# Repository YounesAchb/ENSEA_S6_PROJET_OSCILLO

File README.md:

# ENSEA S6 — Projet Oscilloscope Portable Connecté

Ce dépôt contient l'intégralité des sources (conception matérielle KiCad, firmware STM32 et application Java Android) du projet de fin de S6 réalisé à l'ENSEA. 

## 👥 Étudiants concernés
* **Yassine JABOU**
* **Younes ACHBAD**
* **Gabriel BOUDOUX D'HAUTEFEUILLE**
* **Gökay OZDEN**

---

## 📝 Abstract & Contexte de Fin de Projet
Le but de ce projet est de concevoir un système embarqué autonome agissant comme un oscilloscope de précision déporté. L'écosystème est divisé en deux parties principales :
1. **Un boîtier d'acquisition autonome :** Reçoit le signal analogique, adapte son amplitude, le numérise via un STM32L476RG et transmet les trames via un module Bluetooth HC-05.
2. **Une interface utilisateur (Display) :** Une application Android native développée en Java permettant la visualisation en temps réel, le contrôle des calibres, les mesures par curseurs et le traitement fréquentiel (FFT).

⚠️ **Statut Réel du Projet (Post-Soutenance) :** Suite à un retard de livraison critique de notre fournisseur sur le composant analogique central (l'amplificateur à gain programmable PGA849), le PCB final n'a pas pu être assemblé et soudé à temps pour les tests physiques. 
Cependant, l'ensemble du projet a été validé avec succès par une **approche de virtualisation et de simulation** :
* **Hardware :** PCB double couche entièrement routé et validé par DRC sous KiCad.
* **Firmware C :** 100% fonctionnel, validé sur carte Nucleo en simulant l'absence du PGA.
* **Application Android :** 100% fonctionnelle, dotée d'un banc de simulation générant des signaux virtuels cohérents permettant de valider l'interface utilisateur, le protocole de communication et les algorithmes de traitement (FFT, curseurs).

---

## 🛠 Spécifications du Projet

### 1. Performances & Objectifs Communs
* **Nombre d'entrées :** 2 voies (1 voie implémentée et validée sur cette version).
* **Bande passante visée :** 10 Hz - 50 kHz.
* **Résolution d'acquisition :** 12 bits.
* **Échantillonnage :** 10 kHz fixe, rythmé de manière matérielle par Timer.
* **Points par capture :** Buffer circulaire de 1024 points (gestion par demi-tableaux de 512 points).
* **Communication :** Liaison Bluetooth SPP (Standard Serial Port Profile) à 115200 bauds.
* **Gestion de l'énergie :** Objectif d'autonomie de 6 heures sur piles (sélection de composants Low-Power).

### 2. Architecture Matérielle (Hardware)

Le routage a été optimisé sur un PCB compact double couche. La conception repose sur une séparation stricte des masses et une cascade d'alimentation spécifique pour préserver la propreté du signal de référence ($V_{ref}$) de l'ADC.

#### Schéma Bloc de l'Architecture Électronique
```mermaid
graph TD
    classDef power fill:#2d3436,stroke:#deff9a,stroke-width:2px,color:#fff;
    classDef analog fill:#d63031,stroke:#fff,stroke-width:2px,color:#fff;
    classDef digital fill:#0984e3,stroke:#fff,stroke-width:2px,color:#fff;
    classDef com fill:#00b894,stroke:#fff,stroke-width:2px,color:#fff;

    subgraph Alimentation & Énergie
        Piles((Piles 3xAA)) -->|BAT_PLUS| Switch[Interrupteur + Diode Schottky]
        Switch -->|Vin| LDO3[LDO 3.3V: AP2112K]:::power
        Switch -->|Vin| LDO5[LDO 5V: MCP1826S]:::power
        LDO5 -->|Sortie 5V| Traco[DC/DC Symétrique: Traco TSM]:::power
        Traco -->|+15V / -15V| PGA
    end

    subgraph Chaîne Analogique
        BNC((BNC Verticale 50Ω)) -->|Signal Brut| PGA[Ampli de précision: PGA849]:::analog
        PGA -->|Signal Conditionné| Clamping[Diode de protection: BAT54S]:::analog
        Clamping -->|Entrée Analogique PA0| MCU
    end

    subgraph Traitement & Communication
        LDO3 -->|V3.3_DIG| MCU[MCU: STM32L476RG]:::digital
        MCU -->|Sélection Calibre 3-bits| PGA
        LDO5 -->|5V BT| BT[Module Bluetooth: HC-05]:::com
        MCU <-->|UART 115200 bauds| BT
        BT -.->|Sans-fil SPP| Android((App Android Java)):::com
    end

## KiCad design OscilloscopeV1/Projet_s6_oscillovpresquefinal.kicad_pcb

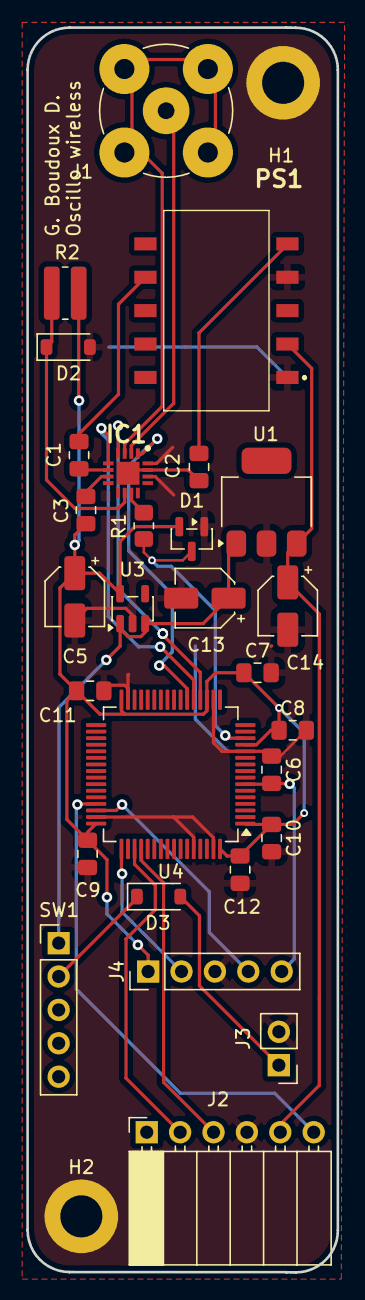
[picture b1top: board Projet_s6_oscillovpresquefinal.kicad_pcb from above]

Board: 2 copper layers, 23.6 x 94.7 mm, 30 parts (0 on the bottom side), 25 nets.

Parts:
C1, C2, C3, C6, C7, C8, C9, C10, C11, C12: 100 nF; C_0805_2012Metric_Pad1.18x1.45mm_HandSolder
C5, C13, C14: 10µ; CP_Elec_4x5.7
D1: BAT54S; SOT-23
D2: D_Zener; D_SOD-123
D3: D_Schottky; D_SOD-123
H1, H2: MountingHole_Pad; MountingHole_3.2mm_M3_DIN965_Pad
IC1: PGA849RGTR; QFN50P300X300X100-17N-D
J1: Conn_Coaxial; BNC_TEConnectivity_1478204_Vertical
J2: Conn_01x06_Socket; PinSocket_1x06_P2.54mm_Horizontal
J3: PILES_3AA; PinHeader_1x02_P2.54mm_Vertical
J4: Conn_01x05_Pin; PinHeader_1x05_P2.54mm_Vertical
PS1: TSM_0515D; TSM0515D
R1: 1k; R_0805_2012Metric_Pad1.20x1.40mm_HandSolder
R2: 1,35k; R_0815_2038Metric_Pad1.20x4.05mm_HandSolder
SW1: SW_SPST; PinHeader_1x05_P2.54mm_Vertical
U1: MCP1826S; SOT-223
U3: AP2112K-3.3; SOT-23-5
U4: STM32L476RGTx; LQFP-64_10x10mm_P0.5mm

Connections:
ANL0: IC1.4 (A0), U4.20 (PA4)
ANL1: IC1.5 (A1), U4.21 (PA5)
ANL2: IC1.1 (A2), U4.22 (PA6)
BAT_PLUS: C13.1, SW1.1 (A), U1.1 (VI), U3.1 (VIN), U3.3 (EN)
Entree_adc: D1.3 (COM), R1.1, U4.14 (PA0)
GND: C5.2, C6.1, C7.2, C8.2, C9.2, C10.2, C11.2, C12.2, C13.2, C14.2, D1.1 (A), D2.2 (A), H1.1, H2.1, IC1.14 (LVSS), IC1.16 (DGND), J2.4, J3.2, J4.3, PS1.1 (-VIN), PS1.7 (COM), U1.2 (GND), U3.2 (GND), U4.12 (VSSA), U4.18 (VSS), U4.31 (VSS), U4.47 (VSS), U4.60 (BOOT0), U4.63 (VSS)
KEY: J2.6, U4.45 (PA12)
NRST: C6.2, J4.5, U4.7 (NRST)
unnamed: D3.2 (A), J3.1
unnamed: D3.1 (K), SW1.2 (B)
unnamed: C2.2, IC1.15 (VS-), IC1.17 (EP)
unnamed: IC1.2 (IN+), J1.1 (In)
unnamed: IC1.3 (IN-), J1.2 (Ext)
unnamed: C3.1, IC1.7 (LVDD)
unnamed: C1.1, IC1.6 (VS+)
SGN_Sortie: IC1.11 (OUT), R1.2
SWCLK: J4.2, U4.49 (PA14)
SWDIO: J4.4, U4.46 (PA13)
Sortie5V: C14.1, J2.5, PS1.3 (+VIN), U1.3 (VO)
Traco_+15V: C1.2, PS1.12 (+VO)
Traco_-15V: C2.1, PS1.9 (-VO)
UART_RX: J2.3, U4.52 (PC11)
UART_TX: J2.2, U4.51 (PC10)
V3.3_DIG: C3.2, C5.1, C7.1, C8.1, C9.1, C10.1, C11.1, C12.1, D1.2 (K), J4.1, R2.1, U3.5 (VOUT), U4.1 (VBAT), U4.13 (VDDA), U4.19 (VDD), U4.32 (VDD), U4.48 (VDDUSB), U4.64 (VDD)
Vref_1.5: D2.1 (K), IC1.10 (REF), R2.2

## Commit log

2026-02-09 Create ALIMENTATION.md
    Descriptif du système d'alimentation
2026-02-09 Update ALIMENTATION.md
    Ajout d'explication pour les 2 résistances de 100kOhm
2026-02-09 Update SOURCING COMPOSANTS - Feuille 1.pdf
    Rajout et mise au propre du sourcing
2026-02-09 name correction
2026-02-16 Ajout de la Librairie des composants
2026-02-16 Addition du schematic partie analogique
2026-02-16 schematic adc v2
    pin for HC05, improvment of pont diviseur
2026-02-16 Partie Alim
    A completer
2026-02-16 Version Presque final du schematics
2026-02-18 Add files via upload
    c'est juste la partie écran
2026-02-18 Add files via upload
    Voici la partie bluetooth
2026-02-18 v4
    Addition of zener instead of op amp for generating 1.5V
2026-02-19 Partie Alim Fini
2026-03-08 Ajout du connecteur SWD et des fixations
2026-03-09 Résolution de toutes les erreurs ERC
2026-03-09 Restructuration de l'architecture du projet
    J'ai mis le schéma dans un projet , il est auparavant appart il se trouve désormais dans le dossier Oscillo_Y
2026-03-09 Ajout des Empreintes pour PGA et pour le Traco ( TSM )
2026-03-09 Plus d'erreur ERC et empreintes du traco et pga
2026-03-09 Restructuration des fichiers
2026-03-09 Ajout du schématique final
2026-03-09 Modification du système d'alimentation / tension de 1,5V
    Modification du système d'alimentation et remplacement du suiveur par une diode zener
2026-03-09 Ajout de toutes les empreintes
2026-03-09 Finalisation Empreinte
2026-03-09 Avancement PCB
2026-03-09 Add files via upload
    Version finale 1. ie : La vesion du projet pcb qui a les bons compos (hopefully)
2026-03-09 Create Sourcing complet
2026-03-16 Avancement PCB : Plans de masse et structuration
2026-03-16 pos mod by A.T.
    pos modifieied by A.T.
2026-03-16 Amincissement du pcb
2026-03-16 Bon de commande finale
2026-03-16 Point de départ du routage
2026-03-21 Add files via upload
    Routage du pcb pour qu'il soit fait en long pour entrer dans la sonde
2026-03-21 Merge pull request #1 from YounesAchb/End-routing
    Add files via upload
2026-03-30 Add files via upload
    routage du pcb the long way
2026-03-30 Add files via upload
    PCB done the long way
2026-03-30 PCB Final
2026-03-30 Start routing (#2)
    * Point de départ du routage
    * Merge pull request #1 from YounesAchb/End-routing
    Add files via upload
    * Add files via upload
    routage du pcb the long way
    * PCB Final
2026-03-30 Nettoyage / suppresion fichiers inutiles
2026-04-16 Add fabrication files
2026-04-17 fab file add
2026-05-21 Create Code en C
2026-05-21 Add files via upload
    Code en C
2026-05-21 Rename Oscillo V1.zip to Code C
2026-05-24 Rename Projet_s6_oscillovpresquefinal.csv to Projet_s6_oscillo.csv
2026-05-24 Rename Projet_s6_oscillovpresquefinal.kicad_pcb to Projet_s6_oscillo.kicad_pcb
2026-05-24 Rename Projet_s6_oscillovpresquefinal.kicad_prl to Projet_s6_oscillo.kicad_prl
2026-05-24 Rename Projet_s6_oscillovpresquefinal.kicad_pro to Projet_s6_oscillo.kicad_pro
2026-05-24 Rename Projet_s6_oscillovpresquefinal.kicad_sch to Projet_s6_oscillo.kicad_sch
2026-05-24 Rename Projet_s6_oscillovpresquefinal.step to Projet_s6_oscillo.step
2026-05-24 Rename _autosave-Projet_s6_oscillovpresquefinal.kicad_prl to _autosave-Projet_s6_oscillo.kicad_prl
2026-05-24 Rename _autosave-Projet_s6_oscillovpresquefinal.kicad_pro to _autosave-Projet_s6_oscillo.kicad_pro
2026-05-24 Rename ~_autosave-Projet_s6_oscillovpresquefinal.kicad_pcb.lck to ~_autosave-Projet_s6_oscillo.kicad_pcb.lck
2026-05-24 Rename Bon_commande_Farnell.xlsx to BonsCommandes/Bon_commande_Farnell.xlsx
2026-05-24 Rename Bon_commande_mouser.xlsx to BonsCommandes/Bon_commande_mouser.xlsx
2026-05-24 Rename Bon_commande_robot-maker.xlsx to BonsCommandes/Bon_commande_robot-maker.xlsx
2026-05-24 Rename bon_commande_RS.xlsx to BonsCommandes/bon_commande_RS.xlsx
